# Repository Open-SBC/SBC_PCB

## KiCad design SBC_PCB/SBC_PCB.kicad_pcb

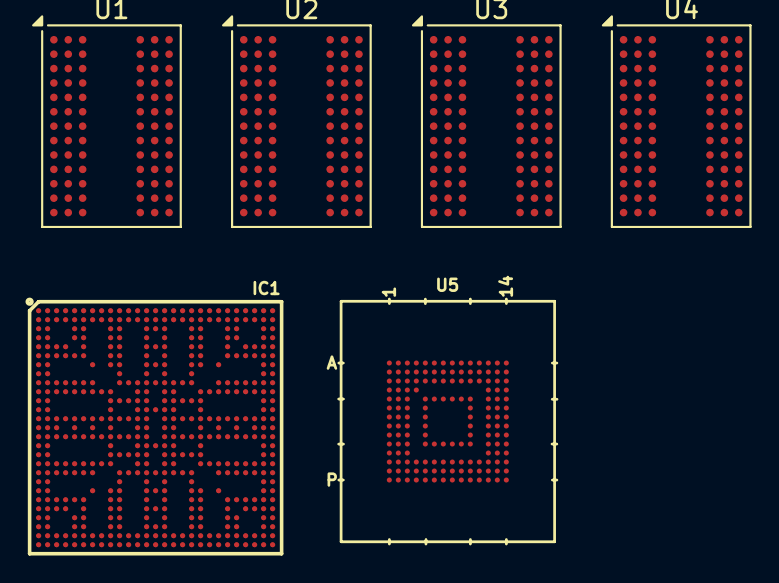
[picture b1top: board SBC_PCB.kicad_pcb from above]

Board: 2 copper layers, 6 parts (0 on the bottom side), 114 nets, no tracks yet.

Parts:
IC1: MIMX8MM5DVTLZDA; BGA486
U1, U2, U3, U4: K4A8G085WD‑BCWE; FBGA-78_7.5x11mm_Layout2x3x13_P0.8mm
U5: EMMC32G-TS0A-01002; FBGA153_13x11.5x0.8

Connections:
/DRAM/A0: IC1.AD5 (DRAM_AC31), U1.L3 (A0), U2.L3 (A0), U3.L3 (A0), U4.L3 (A0)
/DRAM/A1: IC1.U1 (DRAM_AC25), U1.L7 (A1), U2.L7 (A1), U3.L7 (A1), U4.L7 (A1)
/DRAM/A2: IC1.U2 (DRAM_AC24), U1.M3 (A2), U2.M3 (A2), U3.M3 (A2), U4.M3 (A2)
/DRAM/A3: IC1.N6 (DRAM_AC15), U1.K7 (A3), U2.K7 (A3), U3.K7 (A3), U4.K7 (A3)
/DRAM/A4: IC1.K5 (DRAM_AC14), U1.K3 (A4), U2.K3 (A4), U3.K3 (A4), U4.K3 (A4)
/DRAM/A5: IC1.N5 (DRAM_AC13), U1.L8 (A5), U2.L8 (A5), U3.L8 (A5), U4.L8 (A5)
/DRAM/A6: IC1.N4 (DRAM_AC12), U1.L2 (A6), U2.L2 (A6), U3.L2 (A6), U4.L2 (A6)
/DRAM/A7: IC1.E4 (DRAM_AC10), U1.M8 (A7), U2.M8 (A7), U3.M8 (A7), U4.M8 (A7)
/DRAM/A8: IC1.D5 (DRAM_AC11), U1.M2 (A8), U2.M2 (A8), U3.M2 (A8), U4.M2 (A8)
/DRAM/A9: IC1.J5 (DRAM_AC07), U1.M7 (A9), U2.M7 (A9), U3.M7 (A9), U4.M7 (A9)
/DRAM/A10/AP: IC1.AC4 (DRAM_AC30), U1.J3 (A10/AP), U2.J3 (A10/AP), U3.J3 (A10/AP), U4.J3 (A10/AP)
/DRAM/A11: IC1.K6 (DRAM_AC09), U1.N2 (A11), U2.N2 (A11), U3.N2 (A11), U4.N2 (A11)
/DRAM/A12: IC1.J6 (DRAM_AC08), U1.J7 (A12/~BC), U2.J7 (A12/~BC), U3.J7 (A12/~BC), U4.J7 (A12/~BC)
/DRAM/A13: IC1.W6 (DRAM_AC28), U1.N8 (A13), U2.N8 (A13), U3.N8 (A13), U4.N8 (A13)
/DRAM/A14/~WE: IC1.T1 (DRAM_AC34), U1.H2 (A14/~WE), U2.H2 (A14/~WE), U3.H2 (A14/~WE), U4.H2 (A14/~WE)
/DRAM/A15/~CAS: IC1.R5 (DRAM_AC33), U1.H7 (A15/~CAS), U2.H7 (A15/~CAS), U3.H7 (A15/~CAS), U4.H7 (A15/~CAS)
/DRAM/BA0: IC1.V6 (DRAM_AC29), U1.K2 (BA0), U2.K2 (BA0), U3.K2 (BA0), U4.K2 (BA0)
/DRAM/BA1: IC1.N1 (DRAM_AC26), U1.K8 (BA1), U2.K8 (BA1), U3.K8 (BA1), U4.K8 (BA1)
/DRAM/BG0: IC1.L2 (DRAM_AC04), U1.J2 (BG0), U2.J2 (BG0), U3.J2 (BG0), U4.J2 (BG0)
/DRAM/BG1: IC1.L1 (DRAM_AC05), U1.J8 (BG1), U2.J8 (BG1), U3.J8 (BG1), U4.J8 (BG1)
/DRAM/CKE_A: IC1.F4 (DRAM_AC00), U1.G3 (CKE), U2.G3 (CKE)
/DRAM/CKE_B: IC1.F5 (DRAM_AC01), U3.G3 (CKE), U4.G3 (CKE)
/DRAM/CK_A: IC1.M1 (DRAM_AC16), U1.F7 (CK_t), U2.F7 (CK_t)
/DRAM/CK_B: IC1.AB4 (DRAM_AC20), U3.F7 (CK_t), U4.F7 (CK_t)
/DRAM/DQL_0A: IC1.A5 (DRAM_DQ00), U1.C2 (DQ0)
/DRAM/DQL_0B: IC1.AB2 (DRAM_DQ16), U3.C2 (DQ0)
/DRAM/DQL_1A: IC1.B5 (DRAM_DQ01), U1.B7 (DQ1)
/DRAM/DQL_1B: IC1.AA2 (DRAM_DQ17), U3.B7 (DQ1)
/DRAM/DQL_2A: IC1.D2 (DRAM_DQ02), U1.D3 (DQ2)
/DRAM/DQL_2B: IC1.W1 (DRAM_DQ18), U3.D3 (DQ2)
/DRAM/DQL_3A: IC1.D1 (DRAM_DQ03), U1.D7 (DQ3)
/DRAM/DQL_3B: IC1.W2 (DRAM_DQ19), U3.D7 (DQ3)
/DRAM/DQL_4A: IC1.C1 (DRAM_DQ04), U1.D2 (DQ4)
/DRAM/DQL_4B: IC1.V2 (DRAM_DQ20), U3.D2 (DQ4)
/DRAM/DQL_5A: IC1.B1 (DRAM_DQ05), U1.D8 (DQ5)
/DRAM/DQL_5B: IC1.V1 (DRAM_DQ21), U3.D8 (DQ5)
/DRAM/DQL_6A: IC1.A3 (DRAM_DQ06), U1.E3 (DQ6)
/DRAM/DQL_6B: IC1.AC1 (DRAM_DQ22), U3.E3 (DQ6)
/DRAM/DQL_7A: IC1.B4 (DRAM_DQ07), U1.E7 (DQ7)
/DRAM/DQL_7B: IC1.AC2 (DRAM_DQ23), U3.E7 (DQ7)
/DRAM/DQSL_A: IC1.A2 (DRAM_DQS0_P), U1.C3 (DQS_t)
/DRAM/DQSL_B: IC1.AA1 (DRAM_DQS2_P), U3.C3 (DQS_t)
/DRAM/DQSU_A: IC1.G1 (DRAM_DQS1_P), U2.C3 (DQS_t)
/DRAM/DQSU_B: IC1.AG2 (DRAM_DQS3_P), U4.C3 (DQS_t)
/DRAM/DQU_0A: IC1.F2 (DRAM_DQ08), U2.C2 (DQ0)
/DRAM/DQU_0B: IC1.AG5 (DRAM_DQ24), U4.C2 (DQ0)
/DRAM/DQU_1A: IC1.G2 (DRAM_DQ09), U2.B7 (DQ1)
/DRAM/DQU_1B: IC1.AF5 (DRAM_DQ25), U4.B7 (DQ1)
/DRAM/DQU_2A: IC1.J1 (DRAM_DQ10), U2.D3 (DQ2)
/DRAM/DQU_2B: IC1.AD2 (DRAM_DQ26), U4.D3 (DQ2)
/DRAM/DQU_3A: IC1.J2 (DRAM_DQ11), U2.D7 (DQ3)
/DRAM/DQU_3B: IC1.AD1 (DRAM_DQ27), U4.D7 (DQ3)
/DRAM/DQU_4A: IC1.K2 (DRAM_DQ12), U2.D2 (DQ4)
/DRAM/DQU_4B: IC1.AE1 (DRAM_DQ28), U4.D2 (DQ4)
/DRAM/DQU_5A: IC1.K1 (DRAM_DQ13), U2.D8 (DQ5)
/DRAM/DQU_5B: IC1.AF1 (DRAM_DQ29), U4.D8 (DQ5)
/DRAM/DQU_6A: IC1.E1 (DRAM_DQ14), U2.E3 (DQ6)
/DRAM/DQU_6B: IC1.AG3 (DRAM_DQ30), U4.E3 (DQ6)
/DRAM/DQU_7A: IC1.E2 (DRAM_DQ15), U2.E7 (DQ7)
/DRAM/DQU_7B: IC1.AF4 (DRAM_DQ31), U4.E7 (DQ7)
/DRAM/MTEST: IC1.N2 (DRAM_AC19), U1.G9 (TEN), U2.G9 (TEN), U3.G9 (TEN), U4.G9 (TEN)
/DRAM/ODT_A: IC1.V5 (DRAM_AC36), U1.F3 (ODT), U2.F3 (ODT)
/DRAM/ODT_B: IC1.W5 (DRAM_AC37), U3.F3 (ODT), U4.F3 (ODT)
/DRAM/PAR: IC1.R6 (DRAM_AC27), U1.N3 (PAR), U2.N3 (PAR), U3.N3 (PAR), U4.N3 (PAR)
/DRAM/VREF: IC1.P1 (DRAM_VREF), U1.J1 (VREFCA), U2.J1 (VREFCA), U3.J1 (VREFCA), U4.J1 (VREFCA)
/DRAM/ZQ: IC1.P2 (DRAM_ZN), U1.B9 (ZQ), U2.B9 (ZQ), U3.B9 (ZQ), U4.B9 (ZQ)
/DRAM/~ACT: IC1.F6 (DRAM_AC06), U1.H3 (~ACT), U2.H3 (~ACT), U3.H3 (~ACT), U4.H3 (~ACT)
/DRAM/~ALERT: IC1.R2 (DRAM_ALERT_N), U1.L9 (~ALERT), U2.L9 (~ALERT), U3.L9 (~ALERT), U4.L9 (~ALERT)
/DRAM/~CK_A: IC1.M2 (DRAM_AC17), U1.F8 (CK_c), U2.F8 (CK_c)
/DRAM/~CK_B: IC1.AB5 (DRAM_AC21), U3.F8 (CK_c), U4.F8 (CK_c)
/DRAM/~CS_A: IC1.K4 (DRAM_AC02), U1.G7 (~CS), U2.G7 (~CS)
/DRAM/~CS_B: IC1.AB6 (DRAM_AC38), U3.G7 (~CS), U4.G7 (~CS)
/DRAM/~DML_A: IC1.A4 (DRAM_DM0), U1.A7 (TDQS_t/~DM/DBI)
/DRAM/~DML_B: IC1.AB1 (DRAM_DM2), U3.A7 (TDQS_t/~DM/DBI)
/DRAM/~DMU_A: IC1.F1 (DRAM_DM1), U2.A7 (TDQS_t/~DM/DBI)
/DRAM/~DMU_B: IC1.AG4 (DRAM_DM3), U4.A7 (TDQS_t/~DM/DBI)
/DRAM/~DQSL_A: IC1.B2 (DRAM_DQS0_N), U1.B3 (DQS_c)
/DRAM/~DQSL_B: IC1.Y1 (DRAM_DQS2_N), U3.B3 (DQS_c)
/DRAM/~DQSU_A: IC1.H1 (DRAM_DQS1_N), U2.B3 (DQS_c)
/DRAM/~DQSU_B: IC1.AF2 (DRAM_DQS3_N), U4.B3 (DQS_c)
/DRAM/~RAS: IC1.T2 (DRAM_AC35), U1.H8 (~RAS), U2.H8 (~RAS), U3.H8 (~RAS), U4.H8 (~RAS)
/DRAM/~RESET: IC1.R1 (DRAM_RESET_N), U1.L1 (~RESET), U2.L1 (~RESET), U3.L1 (~RESET), U4.L1 (~RESET)
/eMMC/eMMC_CLK: IC1.V26 (SD1_CLK), U5.M6 (CLK)
/eMMC/eMMC_CMD: IC1.V27 (SD1_CMD), U5.M5 (CMD)
/eMMC/eMMC_D0: IC1.Y27 (SD1_DATA0), U5.A3 (DAT0)
/eMMC/eMMC_D1: IC1.Y26 (SD1_DATA1), U5.A4 (DAT1)
/eMMC/eMMC_D2: IC1.T27 (SD1_DATA2), U5.A5 (DAT2)
/eMMC/eMMC_D3: IC1.T26 (SD1_DATA3), U5.B2 (DAT3)
/eMMC/eMMC_D4: IC1.U27 (SD1_DATA4), U5.B3 (DAT4)
/eMMC/eMMC_D5: IC1.U26 (SD1_DATA5), U5.B4 (DAT5)
/eMMC/eMMC_D6: IC1.W27 (SD1_DATA6), U5.B5 (DAT6)
/eMMC/eMMC_D7: IC1.W26 (SD1_DATA7), U5.B6 (DAT7)
/eMMC/eMMC_DS: IC1.R24 (SD1_STROBE), U5.H5 (DS)
/eMMC/~eMMC_RST: IC1.R23 (SD1_RESET_B), U5.K5 (NRST)
GND: U1.A2 (VSSQ), U1.A8 (VSSQ), U1.A9 (VSS), U1.C8 (VSS), U1.D1 (VSSQ), U1.D9 (VSSQ), U1.E1 (VSS), U1.E9 (VSS), U1.G1 (VSS), U1.H9 (VSS), U1.K1 (VSS), U1.K9 (VSS), U1.N1 (VSS), U2.A2 (VSSQ), U2.A8 (VSSQ), U2.A9 (VSS), U2.C8 (VSS), U2.D1 (VSSQ), U2.D9 (VSSQ), U2.E1 (VSS), U2.E9 (VSS), U2.G1 (VSS), U2.H9 (VSS), U2.K1 (VSS), U2.K9 (VSS), U2.N1 (VSS), U3.A2 (VSSQ), U3.A8 (VSSQ), U3.A9 (VSS), U3.C8 (VSS), U3.D1 (VSSQ), U3.D9 (VSSQ), U3.E1 (VSS), U3.E9 (VSS), U3.G1 (VSS), U3.H9 (VSS), U3.K1 (VSS), U3.K9 (VSS), U3.N1 (VSS), U4.A2 (VSSQ), U4.A8 (VSSQ), U4.A9 (VSS), U4.C8 (VSS), U4.D1 (VSSQ), U4.D9 (VSSQ), U4.E1 (VSS), U4.E9 (VSS), U4.G1 (VSS), U4.H9 (VSS), U4.K1 (VSS), U4.K9 (VSS), U4.N1 (VSS), U5.A6 (VSS), U5.C4 (VSS_q), U5.E7 (VSS), U5.G5 (VSS), U5.H10 (VSS), U5.J5 (VSS), U5.K8 (VSS), U5.N2 (VSS_q), U5.N5 (VSS_q), U5.P4 (VSS_q), U5.P6 (VSS_q)
unnamed: IC1.K8 (NVCC_DRAM_1), IC1.K9 (NVCC_DRAM_2), IC1.L9 (NVCC_DRAM_3), IC1.M9 (NVCC_DRAM_4), IC1.N8 (NVCC_DRAM_5), IC1.N9 (NVCC_DRAM_6), IC1.P7 (NVCC_DRAM_7), IC1.R8 (NVCC_DRAM_8), IC1.R9 (NVCC_DRAM_9), IC1.T9 (NVCC_DRAM_10), IC1.U9 (NVCC_DRAM_11), IC1.V8 (NVCC_DRAM_12), IC1.V9 (NVCC_DRAM_13)
unnamed: IC1.AA14 (VDD_ANA0_1P8_2), IC1.Y15 (VDD_ANA0_1P8_1)
unnamed: IC1.N20 (VDD_ANA1_1P8_1), IC1.P19 (VDD_ANA1_1P8_2)
unnamed: IC1.L17 (VDD_ANA_0P8_1), IC1.N17 (VDD_ANA_0P8_2)
unnamed: IC1.R13 (VDD_ARM_1), IC1.R15 (VDD_ARM_2), IC1.T13 (VDD_ARM_3), IC1.T14 (VDD_ARM_4), IC1.T15 (VDD_ARM_5), IC1.U13 (VDD_ARM_6), IC1.U15 (VDD_ARM_7), IC1.V13 (VDD_ARM_8), IC1.V15 (VDD_ARM_9), IC1.V16 (VDD_ARM_10), IC1.W13 (VDD_ARM_11), IC1.W14 (VDD_ARM_12), IC1.W15 (VDD_ARM_13), IC1.W16 (VDD_ARM_14)
unnamed: IC1.J10 (VDD_DRAM_1), IC1.L10 (VDD_DRAM_2), IC1.N10 (VDD_DRAM_3), IC1.R10 (VDD_DRAM_4), IC1.U10 (VDD_DRAM_5), IC1.W10 (VDD_DRAM_6)
unnamed: IC1.P12 (VDD_GPU_1), IC1.R11 (VDD_GPU_2), IC1.U11 (VDD_GPU_3), IC1.V12 (VDD_GPU_4), IC1.W11 (VDD_GPU_5)
unnamed: IC1.K15 (VDD_SOC_1), IC1.K16 (VDD_SOC_2), IC1.L15 (VDD_SOC_3), IC1.L18 (VDD_SOC_4), IC1.M15 (VDD_SOC_5), IC1.N13 (VDD_SOC_6), IC1.N15 (VDD_SOC_7), IC1.N18 (VDD_SOC_8), IC1.R17 (VDD_SOC_9), IC1.R18 (VDD_SOC_10), IC1.U17 (VDD_SOC_11), IC1.U18 (VDD_SOC_12)
unnamed: IC1.K12 (VDD_VPU_1), IC1.K13 (VDD_VPU_2), IC1.L11 (VDD_VPU_3), IC1.L13 (VDD_VPU_4), IC1.M13 (VDD_VPU_5), IC1.M14 (VDD_VPU_6), IC1.N11 (VDD_VPU_7)
unnamed: IC1.A1 (VSS_103), IC1.A27 (VSS_2), IC1.AA7 (VSS_77), IC1.AA9 (VSS_78), IC1.AA10 (VSS_79), IC1.AA13 (VSS_80), IC1.AA15 (VSS_81), IC1.AA18 (VSS_82), IC1.AA19 (VSS_83), IC1.AA21 (VSS_84), IC1.AB3 (VSS_85), IC1.AB25 (VSS_86), IC1.AC3 (VSS_87), IC1.AC25 (VSS_88), IC1.AE2 (VSS_89), IC1.AE5 (VSS_90), IC1.AE6 (VSS_91), IC1.AE9 (VSS_92), IC1.AE10 (VSS_93), IC1.AE13 (VSS_94), IC1.AE14 (VSS_95), IC1.AE15 (VSS_96), IC1.AE18 (VSS_97), IC1.AE19 (VSS_98), IC1.AE22 (VSS_99), IC1.AE23 (VSS_100), IC1.AF3 (VSS_101), IC1.AG1 (VSS_102), IC1.AG27 (VSS_103), IC1.B3 (VSS_3), IC1.B26 (VSS_4), IC1.C2 (VSS_5), IC1.C5 (VSS_6), IC1.C6 (VSS_7), IC1.C9 (VSS_8), IC1.C10 (VSS_9), IC1.C13 (VSS_10), IC1.C14 (VSS_11), IC1.C15 (VSS_12), IC1.C18 (VSS_13), IC1.C19 (VSS_14), IC1.C22 (VSS_15), IC1.C23 (VSS_16), IC1.E3 (VSS_17), IC1.E25 (VSS_18), IC1.F3 (VSS_19), IC1.F25 (VSS_20), IC1.G7 (VSS_21), IC1.G9 (VSS_22), IC1.G10 (VSS_23), IC1.G13 (VSS_24), IC1.G15 (VSS_25), IC1.G18 (VSS_26), IC1.G19 (VSS_27), IC1.G21 (VSS_28), IC1.H2 (VSS_29), IC1.H18 (VSS_30), IC1.J3 (VSS_31), IC1.J7 (VSS_32), IC1.J21 (VSS_33), IC1.J25 (VSS_34), IC1.K3 (VSS_35), IC1.K7 (VSS_36), IC1.K20 (VSS_37), IC1.K21 (VSS_38), IC1.K25 (VSS_39), IC1.L12 (VSS_40), IC1.L16 (VSS_41), IC1.M12 (VSS_42), IC1.M16 (VSS_43), IC1.N3 (VSS_44), IC1.N7 (VSS_45), IC1.N12 (VSS_46), IC1.N16 (VSS_47), IC1.N21 (VSS_48), IC1.N25 (VSS_49), IC1.P3 (VSS_50), IC1.P13 (VSS_51), IC1.P15 (VSS_52), IC1.P21 (VSS_53), IC1.P25 (VSS_54), IC1.R3 (VSS_55), IC1.R7 (VSS_56), IC1.R12 (VSS_57), IC1.R16 (VSS_58), IC1.R20 (VSS_59), IC1.R21 (VSS_60), IC1.R25 (VSS_61), IC1.T12 (VSS_62), IC1.T16 (VSS_63), IC1.U12 (VSS_64), IC1.U16 (VSS_65), IC1.V3 (VSS_66), IC1.V7 (VSS_67), IC1.V21 (VSS_68), IC1.V25 (VSS_69), IC1.W3 (VSS_70), IC1.W7 (VSS_71), IC1.W21 (VSS_72), IC1.W25 (VSS_73), IC1.Y2 (VSS_74), IC1.Y13 (VSS_75), IC1.Y18 (VSS_76)
unnamed: U1.F2 (NC), U1.G2 (NC), U1.G8 (NC), U1.N7 (NC)
unnamed: U2.F2 (NC), U2.G2 (NC), U2.G8 (NC), U2.N7 (NC)
unnamed: U3.F2 (NC), U3.G2 (NC), U3.G8 (NC), U3.N7 (NC)
unnamed: U4.F2 (NC), U4.G2 (NC), U4.G8 (NC), U4.N7 (NC)
VCC: U5.E6 (VCC), U5.F5 (VCC), U5.J10 (VCC), U5.K9 (VCC)
VCC_q: U5.C6 (VCC_q), U5.M4 (VCC_q), U5.N4 (VCC_q), U5.P3 (VCC_q), U5.P5 (VCC_q)
VDD: U1.A1 (VDD), U1.C7 (VDD), U1.F1 (VDD), U1.F9 (VDD), U1.H1 (VDD), U1.J9 (VDD), U1.M1 (VDD), U1.N9 (VDD), U2.A1 (VDD), U2.C7 (VDD), U2.F1 (VDD), U2.F9 (VDD), U2.H1 (VDD), U2.J9 (VDD), U2.M1 (VDD), U2.N9 (VDD), U3.A1 (VDD), U3.C7 (VDD), U3.F1 (VDD), U3.F9 (VDD), U3.H1 (VDD), U3.J9 (VDD), U3.M1 (VDD), U3.N9 (VDD), U4.A1 (VDD), U4.C7 (VDD), U4.F1 (VDD), U4.F9 (VDD), U4.H1 (VDD), U4.J9 (VDD), U4.M1 (VDD), U4.N9 (VDD)
VDDQ: U1.B2 (VDDQ), U1.B8 (VDDQ), U1.C1 (VDDQ), U1.C9 (VDDQ), U1.E2 (VDDQ), U1.E8 (VDDQ), U2.B2 (VDDQ), U2.B8 (VDDQ), U2.C1 (VDDQ), U2.C9 (VDDQ), U2.E2 (VDDQ), U2.E8 (VDDQ), U3.B2 (VDDQ), U3.B8 (VDDQ), U3.C1 (VDDQ), U3.C9 (VDDQ), U3.E2 (VDDQ), U3.E8 (VDDQ), U4.B2 (VDDQ), U4.B8 (VDDQ), U4.C1 (VDDQ), U4.C9 (VDDQ), U4.E2 (VDDQ), U4.E8 (VDDQ)
VPP: U1.B1 (VPP), U1.M9 (VPP), U2.B1 (VPP), U2.M9 (VPP), U3.B1 (VPP), U3.M9 (VPP), U4.B1 (VPP), U4.M9 (VPP)

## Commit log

2025-08-31 Schematic progress
2026-02-22 Project on hold
